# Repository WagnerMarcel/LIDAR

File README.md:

# LIDAR

Studienarbeit während welcher ein komplettes LIDAR System entwickelt werden soll.
Bestandteil dessen ist

- [ ] Entwicklung eines LIDAR Sensors, welcher auf ~10 Meter zuverlässig erkennen kann
- [ ] Entwicklung eines Bewegungssystems für diesen Sensor, welches 2 Winkel verstellen kann
- [ ] Schreiben einer Software zum Starten / Auswerten eines Messvorgangs

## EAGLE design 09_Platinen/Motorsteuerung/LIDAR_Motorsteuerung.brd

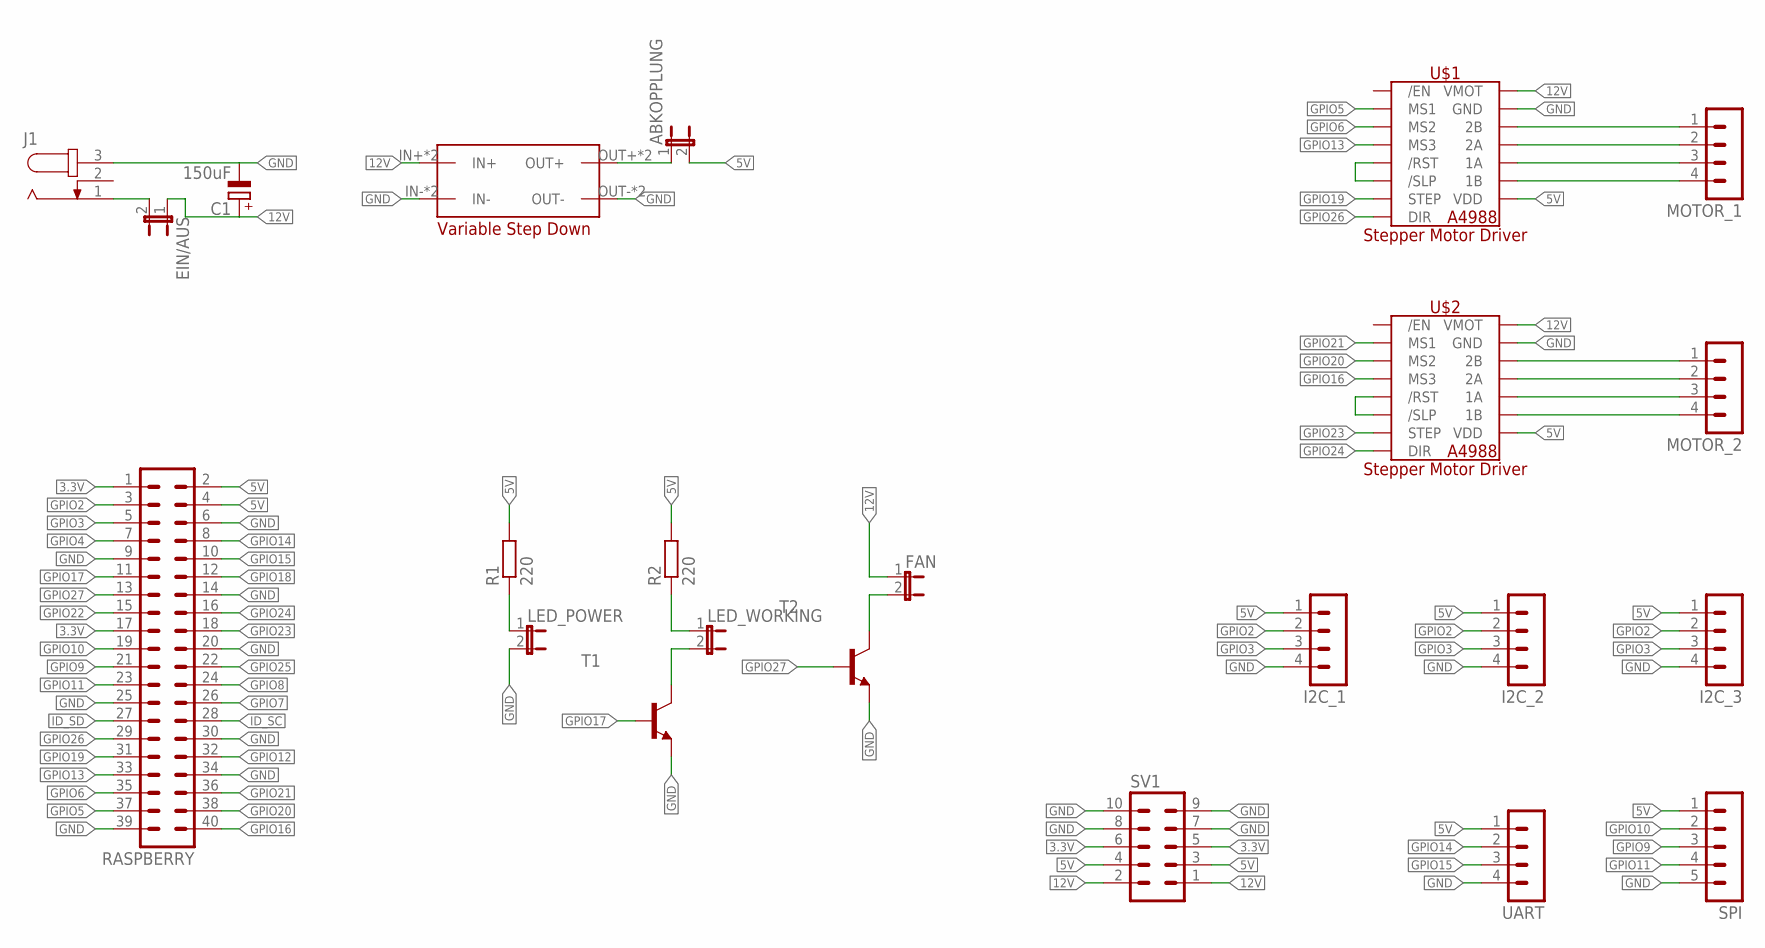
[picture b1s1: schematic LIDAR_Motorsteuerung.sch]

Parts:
ABKOPPLUNG: JP1E; JP1
C1: 150uF; E5-10,5
EIN/AUS: JP1E; JP1
FAN: JP1E; JP1
I2C_1, I2C_2, I2C_3: MA04-1
J1: JACK-PLUG0; SPC4077
LED_POWER: JP1E; JP1
LED_WORKING: JP1E; JP1
MOTOR_1, MOTOR_2: MA04-1
R1, R2: 220; 0207/10
RASPBERRY: MA20-2
SPI: MA05-1
SV1: MA05-2
T1, T2: -NPN-TO92-EBC; TO92-EBC
U$1, U$2: A4988_STEP
U$3: STEP_DOWN
UART: MA04-1

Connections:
3.3V: RASPBERRY.1, RASPBERRY.17, SV1.5, SV1.6
5V: ABKOPPLUNG.2, I2C_1.1, I2C_2.1, I2C_3.1, R1.2, R2.2, RASPBERRY.2, RASPBERRY.4, SPI.1, SV1.3, SV1.4, U$1.VDD, U$2.VDD, UART.1
12V: C1.+, EIN/AUS.1, FAN.1, SV1.1, SV1.2, U$1.VMOT, U$2.VMOT, U$3.IN+, U$3.IN+2 (IN+)
GND: C1.-, I2C_1.4, I2C_2.4, I2C_3.4, J1.3, LED_POWER.2, RASPBERRY.6, RASPBERRY.9, RASPBERRY.14, RASPBERRY.20, RASPBERRY.25, RASPBERRY.30, RASPBERRY.34, RASPBERRY.39, SPI.5, SV1.7, SV1.8, SV1.9, SV1.10, T1.E, T2.E, U$1.GND, U$1.GND2 (GND), U$2.GND, U$2.GND2 (GND), U$3.IN-, U$3.IN-2 (IN-), U$3.OUT-, U$3.OUT-2 (OUT-), UART.4
GPIO2: I2C_1.2, I2C_2.2, I2C_3.2, RASPBERRY.3
GPIO3: I2C_1.3, I2C_2.3, I2C_3.3, RASPBERRY.5
GPIO4: RASPBERRY.7
GPIO5: RASPBERRY.37, U$1.MS1
GPIO6: RASPBERRY.35, U$1.MS2
GPIO7: RASPBERRY.26
GPIO8: RASPBERRY.24
GPIO9: RASPBERRY.21, SPI.3
GPIO10: RASPBERRY.19, SPI.2
GPIO11: RASPBERRY.23, SPI.4
GPIO12: RASPBERRY.32
GPIO13: RASPBERRY.33, U$1.MS3
GPIO14: RASPBERRY.8, UART.2
GPIO15: RASPBERRY.10, UART.3
GPIO16: RASPBERRY.40, U$2.MS3
GPIO17: RASPBERRY.11, T1.B
GPIO18: RASPBERRY.12
GPIO19: RASPBERRY.31, U$1.STEP
GPIO20: RASPBERRY.38, U$2.MS2
GPIO21: RASPBERRY.36, U$2.MS1
GPIO22: RASPBERRY.15
GPIO23: RASPBERRY.18, U$2.STEP
GPIO24: RASPBERRY.16, U$2.DIR
GPIO25: RASPBERRY.22
GPIO26: RASPBERRY.29, U$1.DIR
GPIO27: RASPBERRY.13, T2.B
ID_SC: RASPBERRY.28
ID_SD: RASPBERRY.27
unnamed: U$1./RST, U$1./SLP
unnamed: LED_POWER.1, R1.1
unnamed: MOTOR_1.1, U$1.2B
unnamed: MOTOR_1.2, U$1.2A
unnamed: MOTOR_1.3, U$1.1A
unnamed: MOTOR_1.4, U$1.1B
unnamed: LED_WORKING.1, R2.1
unnamed: LED_WORKING.2, T1.C
unnamed: EIN/AUS.2, J1.1
unnamed: MOTOR_2.1, U$2.2B
unnamed: MOTOR_2.2, U$2.2A
unnamed: MOTOR_2.3, U$2.1A
unnamed: MOTOR_2.4, U$2.1B
unnamed: FAN.2, T2.C
unnamed: U$2./RST, U$2./SLP
NET2: ABKOPPLUNG.1, U$3.OUT+, U$3.OUT+2 (OUT+)

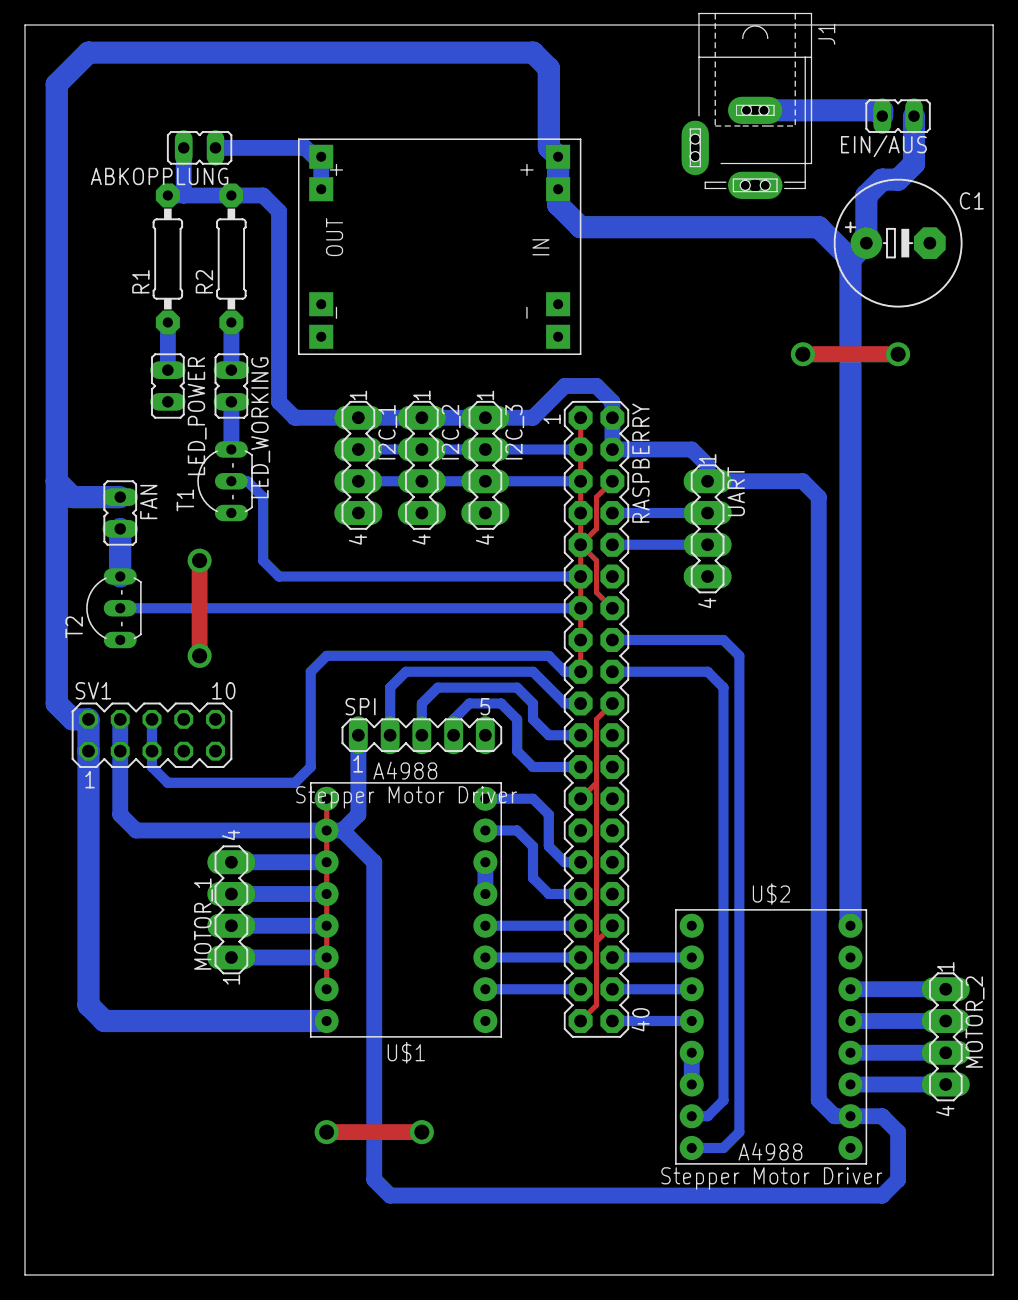
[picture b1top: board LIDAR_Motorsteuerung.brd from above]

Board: 2 copper layers, 77.5 x 100.0 mm, 23 parts (0 on the bottom side), 39 nets.

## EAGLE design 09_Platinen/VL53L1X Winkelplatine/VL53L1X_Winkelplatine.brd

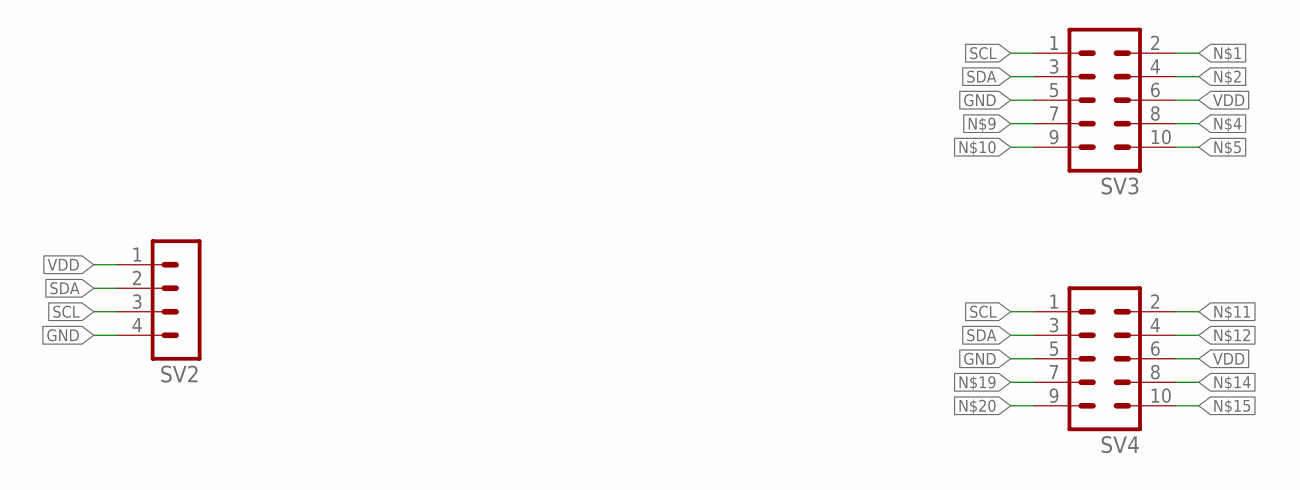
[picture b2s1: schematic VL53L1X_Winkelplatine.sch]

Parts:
SV2: MA04-1
SV3, SV4: MA05-2

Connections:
GND: SV2.4, SV3.5, SV4.5
SCL: SV2.3, SV3.1, SV4.1
SDA: SV2.2, SV3.3, SV4.3
VDD: SV2.1, SV3.6, SV4.6

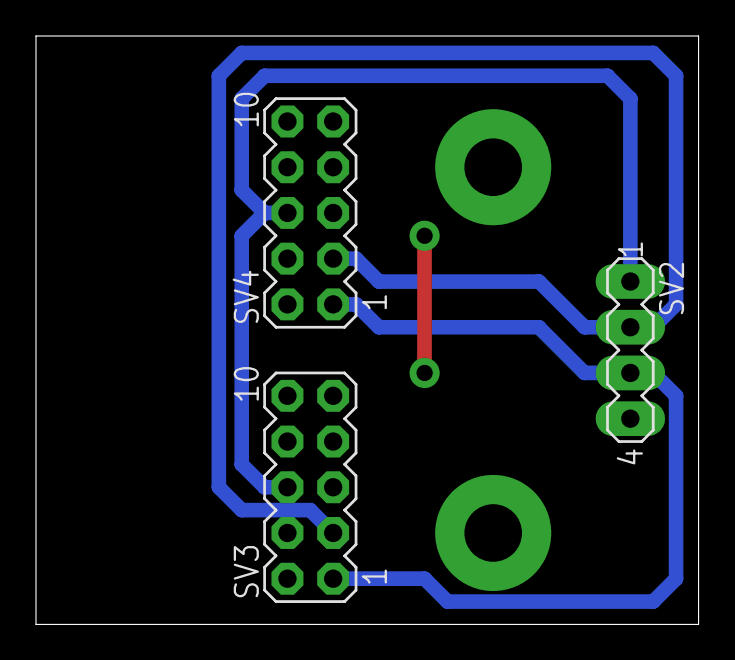
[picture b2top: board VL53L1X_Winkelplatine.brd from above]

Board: 2 copper layers, 36.8 x 32.7 mm, 3 parts (0 on the bottom side), 4 nets.

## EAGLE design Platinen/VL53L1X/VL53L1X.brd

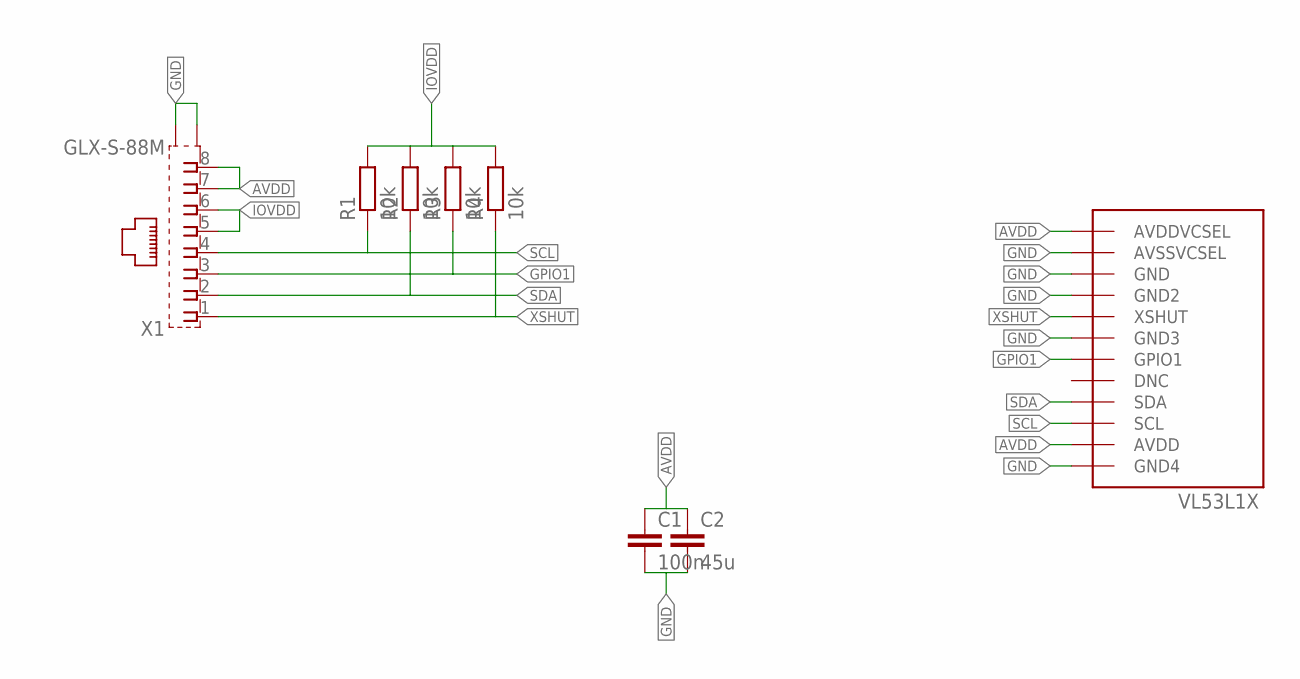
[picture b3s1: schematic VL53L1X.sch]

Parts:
C1: 100n; C0603
C2: 45u; C0603
R1, R2, R3, R4: 10k; R0603
U$1: VL53L1X
X1: GLX-S-88M

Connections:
AVDD: C1.1, C2.1, U$1.AVDD, U$1.AVDDVCSEL, X1.7, X1.8
GND: C1.2, C2.2, U$1.AVSSVCSEL, U$1.GND, U$1.GND2, U$1.GND3, U$1.GND4, X1.S1, X1.S2
GPIO1: R3.1, U$1.GPIO1, X1.3
IOVDD: R1.2, R2.2, R3.2, R4.2, X1.5, X1.6
SCL: R1.1, U$1.SCL, X1.4
SDA: R2.1, U$1.SDA, X1.2
XSHUT: R4.1, U$1.XSHUT, X1.1

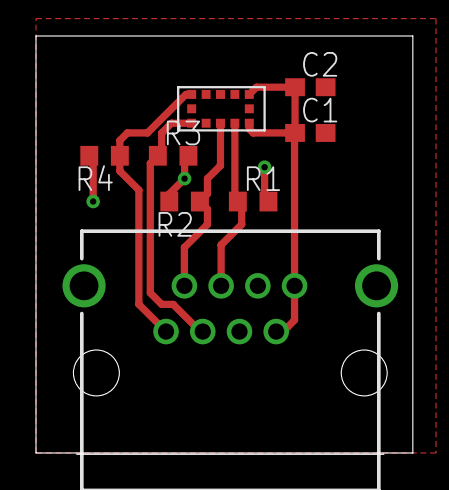
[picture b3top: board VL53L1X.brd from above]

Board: 2 copper layers, 20.9 x 23.2 mm, 8 parts (1 on the bottom side), 7 nets.

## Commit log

2018-10-05 Latex files für Dokumentation
2018-10-05 Anpassungen ans Latex Template
2018-10-05 Kapitel angepasst
2018-10-08 Protokolle
2018-10-08 Readme aktualisiert
2018-10-09 Photo hinzugefügt
2018-10-16 Anmeldung Studienarbeit
2018-10-16 Anmeldung aktualisiert
2018-10-17 Stückliste und Anmeldung aktualisiert
2018-10-17 sdiajfbasiöfjb
2018-10-19 Anmeldung Studienarbeit Final
2018-10-19 Platine für VL53L1X
    Schaltplan, Platine und Stückliste erstellt/aktualisiert
2018-10-20 Zusammenfassung VL53L1X
2018-10-23 Matlab Modell
2018-10-23 Matlab Modell Fertiggestellt
    Kann nun eine 6m x 3m Wand bei welcher im Abstand von 2,5m der Sensor aufgebaut wird. Die Entstehende Punktewolke auf der Wand simulieren. Verschiedene Parametereinstellungen ergeben verschiedene Pun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
2018-10-26 Zeichnungen Hinzugefügt
2018-10-26 Zeichnung Aktualisiert
2018-10-30 Ordnerbezeichnungen
2018-11-09 Mechanik in Latex
2018-11-09 Protokoll 9.11
2018-11-09 Stückliste überarbeitet
2018-11-11 Zeichnungen neue Bauteile
2018-11-11 Zeichnung Rahmen
2018-11-14 Dateien für Herr Geiger
2019-01-22 Anpassungen
    Python Code agepasst
    Matlab Code angepasst
    Gliederung der Dokumentation festgelegt
2019-01-22 Dokumentation
    Kapitel Code
2019-01-25 Kapitel Code
2019-01-28 Eagle Dateien für Motorsteuerung und Winkelplatine
2019-02-03 Kapitel Grundlagen
    Potodiode & Lichtlaufzeitmessung
2019-02-03 Grundlagen + Hardware
2019-02-09 Auswertung + neue Messwerte
2019-02-09 Auswertung
2019-02-11 Originaldateien Raspi
2019-02-11 Grundriss Flur, Daten Vlx
2019-02-11 Änderungen Kapitel Code
2019-02-14 Validierung + viele Bilder
2019-02-17 Kapitel Hardware -Sensoren überarbeitet
2019-02-18 Meine Quellen im richtigen Format
2019-02-18 Kapitel Code fertig
2019-02-18 Kapitel Mechanik fertig
2019-02-18 Anpassungen nach Merge
2019-02-21 Kapitel Grundlagen Laserentfernungsmessung
2019-03-04 Anpassungen Vortrag Umfeldsensorik
2019-05-05 Machbarkeitsstudie & Ausblick
2019-05-11 Frühere Änderungen
2019-05-11 Revert "Frühere Änderungen"
    This reverts commit c52b2748b4ca4d17d4e9338c59a7d13baeb44322.
2019-05-11 Test
2019-05-11 Frühere Änderungen eingefügt Hardware A4988
2019-05-11 Hardware "fertig"
2019-05-11 Auswertung und Darstellung mit Matlab "fertig"
2019-05-11 Matlab Modell (Winkelanpassung) Auswertung
2019-05-13 Aktualisierungen im Code
2019-05-25 Einleitung/Fazit (Grundgerüst)
2019-05-26 Ausblick & Tabellen überarbeitet
2019-05-26 Anpassungen Auswertung + neue Bilder
2019-05-26 Änderungen in Validierung
2019-06-03 Schrittmotoren, Validierung
2019-06-03 Auto stash before merge of "master" and "origin/master"
2019-06-03 Korrektur V1
2019-06-03 Korrektur V2
2019-06-04 Änderungen Marcel bis auf Listings fertig
2019-06-04 Fazit / Korrektur bis Machbarkeitsstudie
2019-06-05 Korrektur bis Seite 52
2019-06-05 Korrektur bis S.70
2019-06-05 Korrektur "fertig"
2019-06-06 Formatierung
2019-06-07 Formatierung Final
